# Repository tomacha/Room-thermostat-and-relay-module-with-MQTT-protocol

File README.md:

# Room-thermostat-and-relay-module-with-MQTT-protocol

This project is a part of smart home system based on MQTT protocol for comunication. Thermostat is battery operated. To comunicate with relay module it uses Bluetooth Low Energy. Relay module comunicates by Wi-Fi with MQTT Broker. It also works as a gate between Broker and Thermostat.

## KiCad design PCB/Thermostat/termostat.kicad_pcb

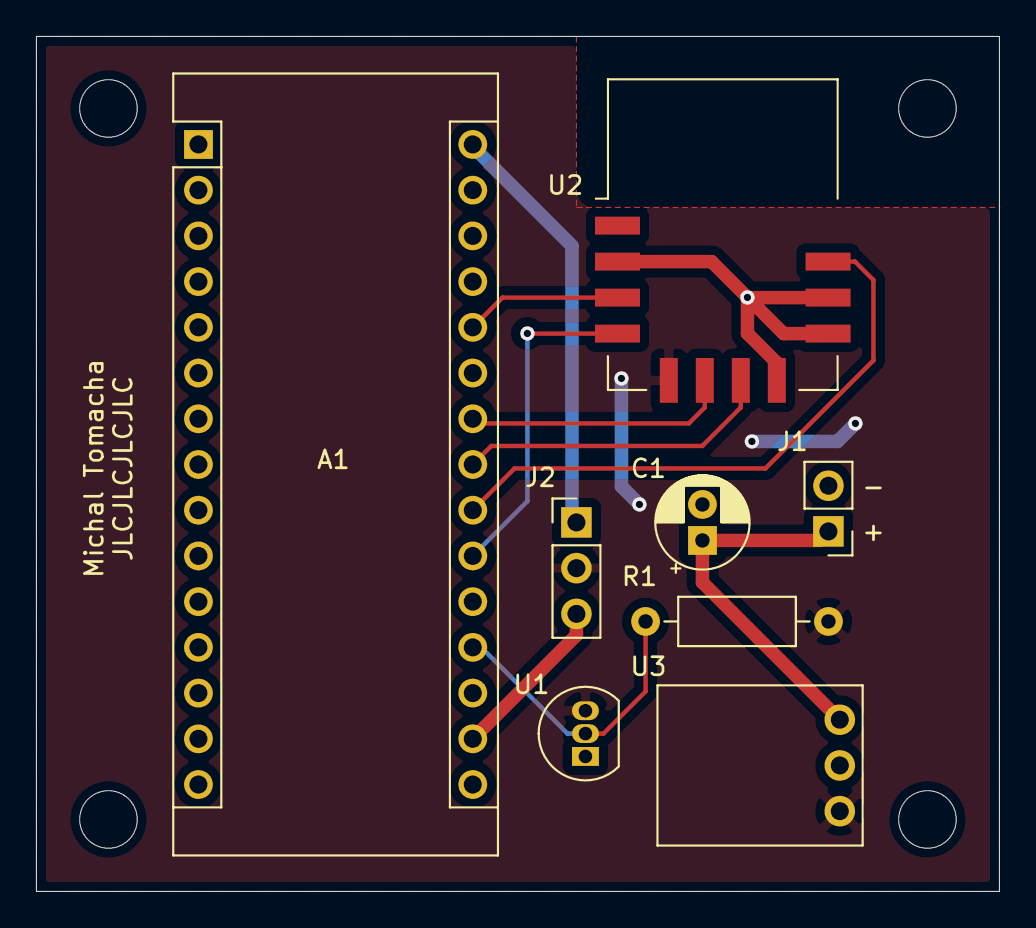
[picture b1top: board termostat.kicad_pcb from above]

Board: 2 copper layers, 53.5 x 47.5 mm, 8 parts (0 on the bottom side), 11 nets.

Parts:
A1: STM32L432KC Nucleo-32; Arduino_Nano
C1: 33u; CP_Radial_D5.0mm_P2.00mm
J1: Batt Conn; PinHeader_1x02_P2.54mm_Vertical
J2: MC_PWR_SEL; PinHeader_1x03_P2.54mm_Vertical
R1: 4,7k; R_Axial_DIN0207_L6.3mm_D2.5mm_P10.16mm_Horizontal
U1: DS18B20; TO-92_Inline
U2: HM-BT4502
U3: U1V10F3

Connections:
3V3: A1.17, J2.3
+3V3: J2.2, R1.1, U1.3, U2.7, U3.1
+BATT: C1.1, J1.1, U3.3
DQ: A1.19, R1.2, U1.2
GND: A1.4, A1.29, C1.2, J1.2, U1.1, U2.2, U2.3, U2.4, U2.10, U3.2
INT: A1.22, U2.1
PDN: A1.23, U2.5
RXD: A1.21, U2.8
TXD: A1.26, U2.9
VIN: A1.30, J2.1
WAKEUP: A1.24, U2.6

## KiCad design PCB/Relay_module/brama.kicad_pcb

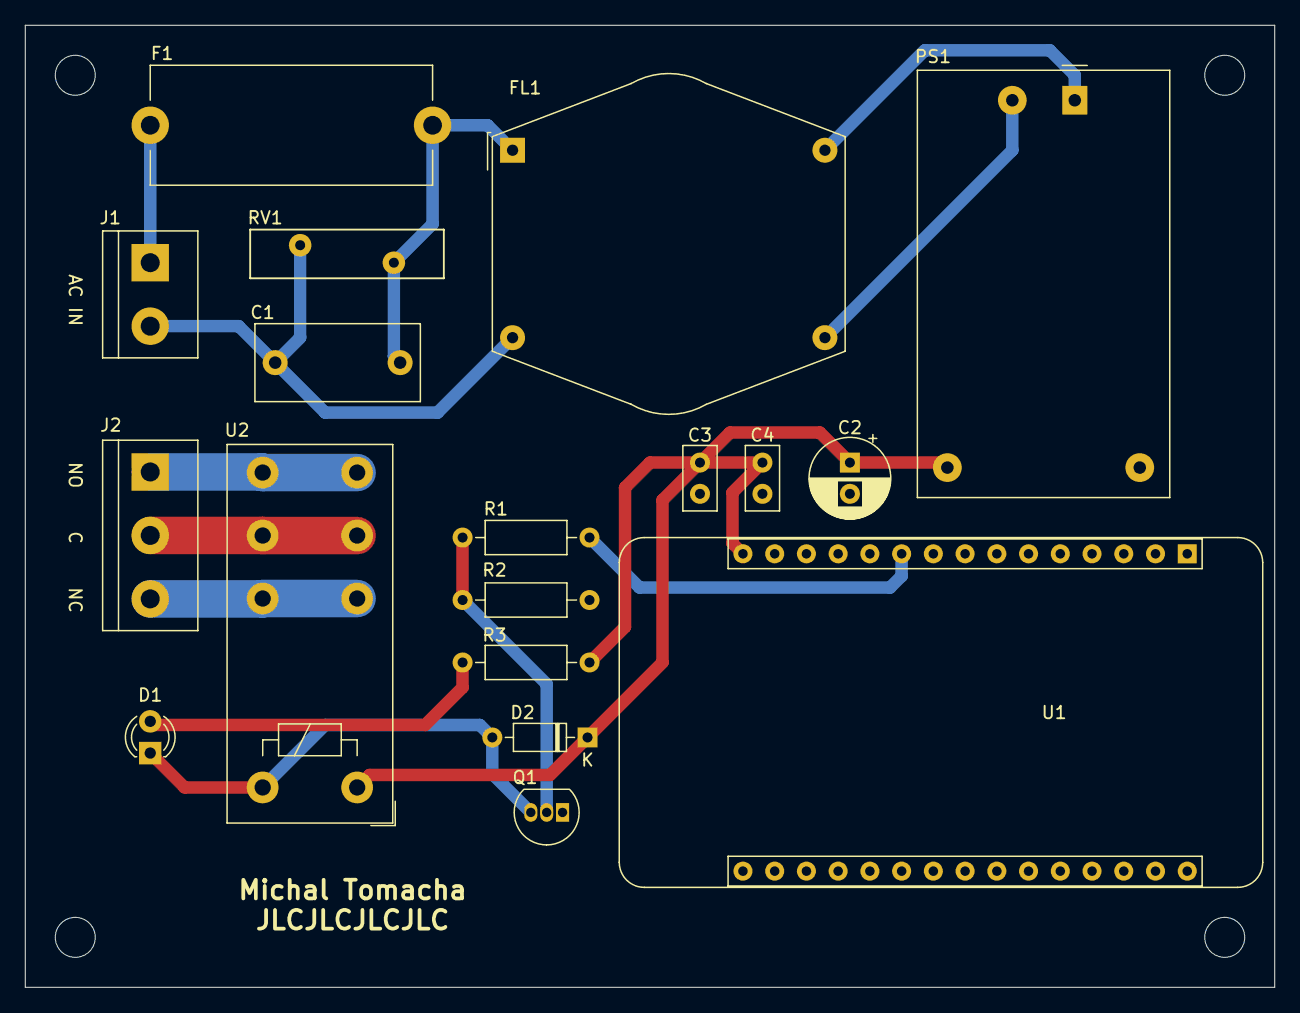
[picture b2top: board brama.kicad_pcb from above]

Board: 2 copper layers, 100.0 x 77.0 mm, 18 parts (0 on the bottom side), 14 nets.

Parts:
C1: C; C_Rect_L13.0mm_W6.0mm_P10.00mm_FKS3_FKP3_MKS4
C2: CP; CP_Radial_D6.3mm_P2.50mm
C3, C4: C; C_Disc_D5.0mm_W2.5mm_P2.50mm
D1: LED; LED_D3.0mm
D2: D; D_DO-35_SOD27_P7.62mm_Horizontal
F1: Fuse; Fuseholder_Cylinder-5x20mm_Stelvio-Kontek_PTF78_Horizontal_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
FL1: EMI_Filter_CommonMode; Choke_Schaffner_RN122-04-28.0x27.0mm
J1: Screw_Terminal_01x02; TerminalBlock_bornier-2_P5.08mm
J2: Screw_Terminal_01x03; TerminalBlock_bornier-3_P5.08mm
PS1: HLK-PM01; Converter_ACDC_HiLink_HLK-PMxx
Q1: Q_NPN_EBC; TO-92_Inline
R1, R2, R3: R; R_Axial_DIN0207_L6.3mm_D2.5mm_P10.16mm_Horizontal
RV1: Varistor; RV_Disc_D15.5mm_W3.9mm_P7.5mm
U1: ESP32_DevKit_V1_DOIT; esp32_devkit_v1_doit
U2: MPI-S-105-C-3

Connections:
+5V: C2.1, C3.1, C4.1, D2.1, PS1.4, R3.1, U1.15, U2.2
GND: C2.2, C3.2, C4.2, PS1.3, Q1.1, R2.2, U1.14, U1.17
MCU: R1.1, U1.10
unnamed: C1.1, F1.2, FL1.1, RV1.1
unnamed: C1.2, FL1.3, J1.2, RV1.2
unnamed: D1.1, D2.2, Q1.3, U2.1
unnamed: D1.2, R3.2
unnamed: F1.1, J1.1
unnamed: FL1.2, PS1.1
unnamed: FL1.4, PS1.2
unnamed: J2.1, U2.5
unnamed: J2.2, U2.3
unnamed: J2.3, U2.4
unnamed: Q1.2, R1.2, R2.1

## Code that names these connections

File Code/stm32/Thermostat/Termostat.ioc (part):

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Mcu.Name=STM32L432K(B-C)Ux
Mcu.Package=UFQFPN32
Mcu.UserName=STM32L432KCUx
PA0.GPIOParameters=GPIO_Label
PA0.GPIO_Label=DS18B20
PA0.Signal=GPIO_Output
PA2.GPIOParameters=GPIO_PuPd
PA2.GPIO_PuPd=GPIO_NOPULL
PA2.Mode=Asynchronous
PA2.Signal=LPUART1_TX
PA3.Mode=Asynchronous
PA3.Signal=LPUART1_RX
PA4.GPIOParameters=GPIO_Label,GPIO_ModeDefaultEXTI
PA4.GPIO_Label=INT
PA4.GPIO_ModeDefaultEXTI=GPIO_MODE_IT_RISING_FALLING
PA4.Signal=GPXTI4
PA5.GPIOParameters=GPIO_Label
PA5.GPIO_Label=PDN
PA5.Signal=GPIO_Output
PA6.GPIOParameters=GPIO_Label
PA6.GPIO_Label=WAKEUP
PA6.Signal=GPIO_Output
PC14-OSC32_IN\ (PC14).Mode=LSE-External-Oscillator
PC14-OSC32_IN\ (PC14).Signal=RCC_OSC32_IN
PC15-OSC32_OUT\ (PC15).Mode=LSE-External-Oscillator
PC15-OSC32_OUT\ (PC15).Signal=RCC_OSC32_OUT
RCC.HSE_VALUE=8000000
RCC.SYSCLKFreq_VALUE=16000000
RCC.SYSCLKSource=RCC_SYSCLKSOURCE_HSI
board=NUCLEO-L432KC
boardIOC=true

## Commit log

2022-03-27 Added all
